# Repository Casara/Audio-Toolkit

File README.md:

# Audio-Toolkit

Uma coleção de módulos de áudio para projetos DIY e de código aberto.

O **Audio-Toolkit** é um repositório de módulos eletrônicos de código aberto, projetados para a construção de projetos de áudio personalizados. Cada módulo é independente e pode ser combinado para criar sistemas completos, como mesas de som ou consoles de áudio.

## Como Contribuir

Contribuições são muito bem-vindas! Se você deseja ajudar a melhorar o projeto, por favor, leia o [Guia de Contribuição](CONTRIBUTING.md) para saber mais sobre os padrões e fluxo de trabalho.

## Licença

Este projeto é de código aberto e está licenciado sob a [CERN Open Hardware Licence (CERN-OHL-P)](LICENSE.txt).

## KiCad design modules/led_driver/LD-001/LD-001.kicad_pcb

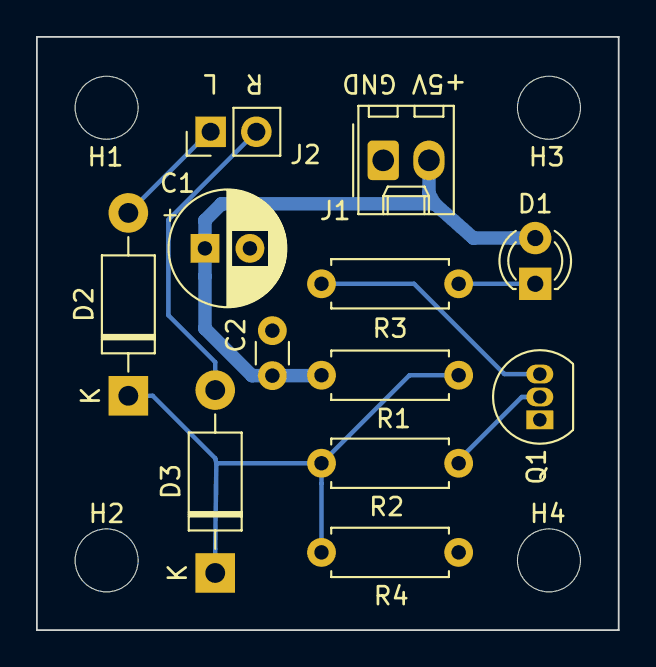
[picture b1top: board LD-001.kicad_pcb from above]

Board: 2 copper layers, 32.3 x 33.0 mm, 16 parts (0 on the bottom side), 8 nets.

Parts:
C1: 47µF; CP_Radial_D6.3mm_P2.50mm
C2: 100nF; C_Disc_D3.0mm_W1.6mm_P2.50mm
D1: LED; LED_D3.0mm
D2, D3: 1N5819; D_DO-41_SOD81_P10.16mm_Horizontal
H1, H2, H3, H4: MountingHole; MountingHole_3.5mm
J1: KK 5045-2 Male 2.5mm 180°; Molex_KK-254_AE-6410-02A_1x02_P2.54mm_Vertical
J2: Conn_01x02; PinHeader_1x02_P2.54mm_Vertical
Q1: 2N3904; TO-92_Inline
R1, R2: 10kΩ; R_Axial_DIN0207_L6.3mm_D2.5mm_P7.62mm_Horizontal
R3: 280Ω; R_Axial_DIN0207_L6.3mm_D2.5mm_P7.62mm_Horizontal
R4: 100kΩ; R_Axial_DIN0207_L6.3mm_D2.5mm_P7.62mm_Horizontal

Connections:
+5V: C1.1, C2.2, D1.2, J1.2, R1.1
GNDREF: C1.2, C2.1, J1.1, Q1.1, R4.2
unnamed: D1.1, R3.1
unnamed: D2.1, D3.1, R1.2, R2.1, R4.1
unnamed: D2.2, J2.1
unnamed: D3.2, J2.2
unnamed: Q1.2, R2.2
unnamed: Q1.3, R3.2

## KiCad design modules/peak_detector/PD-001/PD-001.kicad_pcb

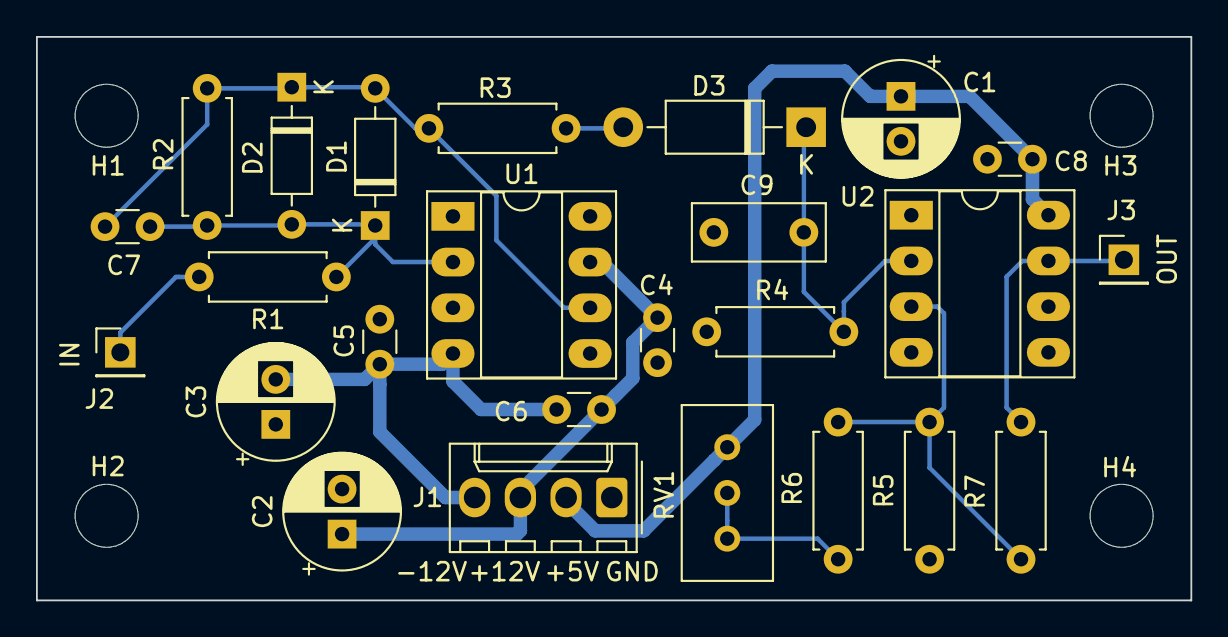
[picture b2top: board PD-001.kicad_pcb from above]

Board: 2 copper layers, 64.1 x 31.3 mm, 29 parts (0 on the bottom side), 12 nets.

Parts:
C1, C2, C3: 47µF; CP_Radial_D6.3mm_P2.50mm
C4, C5, C8: 100nF; C_Disc_D3.0mm_W1.6mm_P2.50mm
C6: 10nF; C_Disc_D3.0mm_W1.6mm_P2.50mm
C7: 10pF; C_Disc_D3.0mm_W1.6mm_P2.50mm
C9: 2.2µF; C_Rect_L7.2mm_W3.0mm_P5.00mm_FKS2_FKP2_MKS2_MKP2
D1, D2: 1N4148; D_DO-35_SOD27_P7.62mm_Horizontal
D3: 1N5819; D_DO-41_SOD81_P10.16mm_Horizontal
H1, H2, H3, H4: MountingHole; MountingHole_3.5mm
J1: KK 5045-4 Male 2.5mm 180°; Molex_KK-254_AE-6410-04A_1x04_P2.54mm_Vertical
J2, J3: Conn_01x01; PinHeader_1x01_P2.54mm_Vertical
R1, R2, R5, R6: 10kΩ; R_Axial_DIN0207_L6.3mm_D2.5mm_P7.62mm_Horizontal
R3: 330Ω; R_Axial_DIN0207_L6.3mm_D2.5mm_P7.62mm_Horizontal
R4: 220kΩ; R_Axial_DIN0207_L6.3mm_D2.5mm_P7.62mm_Horizontal
R7: 100kΩ; R_Axial_DIN0207_L6.3mm_D2.5mm_P7.62mm_Horizontal
RV1: 50kΩ; Potentiometer_Bourns_3296W_Vertical
U1: TL071; DIP-8_W7.62mm_Socket_LongPads
U2: LM311; DIP-8_W7.62mm_Socket_LongPads

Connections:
+5V: C1.1, C8.1, J1.2, RV1.1, U2.8
+12V: C2.1, C4.1, C6.1, J1.3, U1.7
-12V: C3.2, C5.2, C6.2, J1.4, U1.4
GNDREF: C1.2, C2.2, C3.1, C4.2, C5.1, C8.2, C9.2, J1.1, R4.2, R5.2, U1.3, U2.1, U2.4
unnamed: C7.1, D1.1, D2.2, R1.1, R2.2, U1.2
unnamed: C7.2, D1.2, D2.1, R2.1, R3.2, U1.6
unnamed: C9.1, D3.1, R4.1, U2.2
unnamed: D3.2, R3.1
unnamed: J2.1, R1.2
unnamed: J3.1, R7.1, U2.7
unnamed: R5.1, R6.2, R7.2, U2.3
unnamed: R6.1, RV1.2, RV1.3

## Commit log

2025-08-29 🌟 feat(docs): Adiciona a documentação inicial do projeto.
2025-08-29 🧹 chore: Adiciona arquivos de backup e cache do KiCad ao .gitignore.
2025-08-29 🌟 feat(PD-001): Adiciona o design inicial do Peak Detector.
2025-08-29 🌟 feat(LD-002): Adiciona o design inicial do LED Driver.
